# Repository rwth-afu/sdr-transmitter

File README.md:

## Components

### Microcontroller: ST STM32F429VGT6
- ARM Cortex M4 core with DSP and FPU
- 180 MHz cpu clock
- 1 MB flash memory
- 2x 1Msps 12 bit D/A converters (up to 5Msps, see [AN4566](http://www.st.com/resource/en/application_note/dm00129215.pdf))
- USB 2.0 controller
- 10/100 Ethernet MAC
- [Datasheet](http://www.st.com/resource/en/datasheet/stm32f427vg.pdf)

### IQ Modulator: Analog Devices ADRF6755
- Integrated fractional-N PLL & VCO
- Gain control span: 47 dB in 1 dB steps
- Frequency Range: 100 - 2400 MHz
- P1dB (typ @ 1800 MHz): 8 dBm
- Baseband modulation bandwidth: 600 MHz
- [Datasheet](http://www.analog.com/media/en/technical-documentation/data-sheets/ADRF6755.pdf)

### PA Driver: NXP BGA7027
- Frequency Range: 400 - 2700 MHz
- Gain (typ @ 940 MHz): 19 dB
- P1dB (typ @ 940 MHz): 29 dBm
- [Datasheet](https://www.nxp.com/docs/en/data-sheet/BGA7027.pdf)

### Power Amplifier: NXP AFT09MS015N
- Frequency Range: 136 - 941 MHz
- Power Output (typ): 16 W
- Gain (typ): 17 dB
- [Datasheet](https://www.nxp.com/docs/en/data-sheet/AFT09MS015N.pdf)

### Power Detector: Analog Devices AD8364 (*optional*)
- Frequency Range: LF - 2700 MHz
- Dual-channel and channel difference output port
- 60 dB dynamic range
- Maximum input level: 12 dBm
- [Datasheet](http://www.analog.com/media/en/technical-documentation/data-sheets/AD8364.pdf)

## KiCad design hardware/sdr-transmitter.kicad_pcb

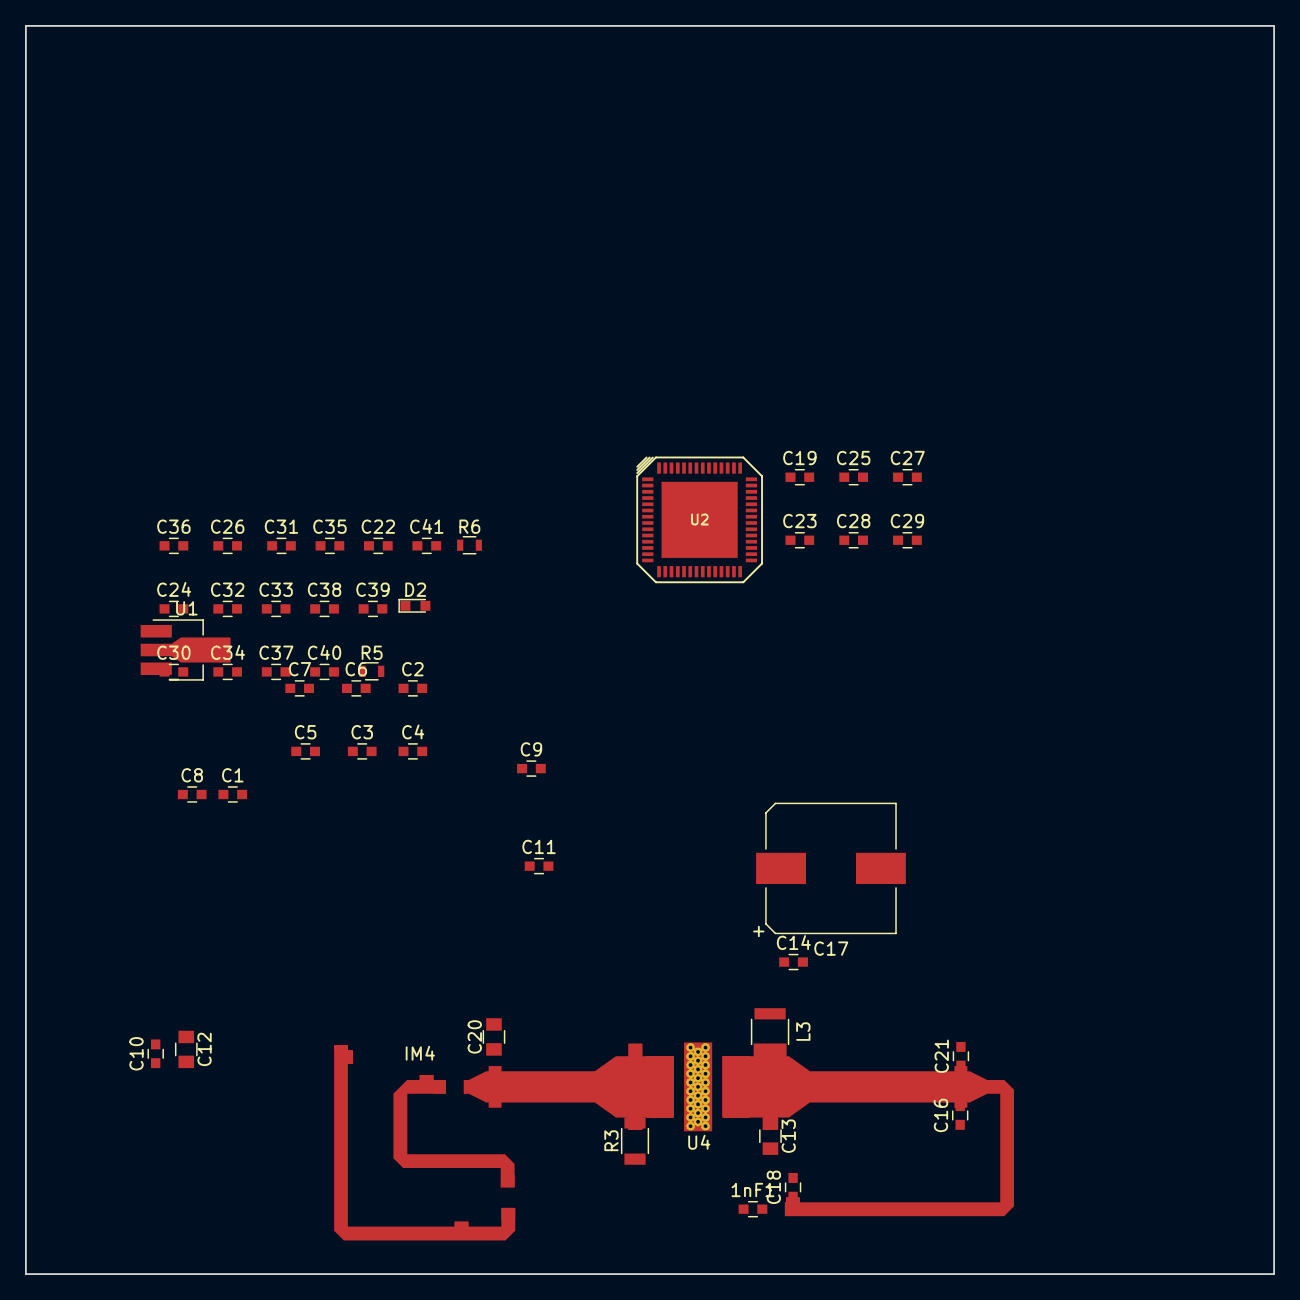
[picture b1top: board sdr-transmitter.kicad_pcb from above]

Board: 2 copper layers, 100.0 x 100.0 mm, 53 parts (0 on the bottom side), 17 nets, no tracks yet.

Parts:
1nF1: C; C_0603
C1, C8: 1nF; C_0603
C2: 10pF; C_0603
C3: 33pF; C_0603
C4, C10, C19, C22, C24, C26, C28, C30, C31, C32, C34, C36, C38, C40: 100n; C_0603
C5: 100nF; C_0603
C6: 100pF; C_0603
C7, C23, C25, C27, C29, C33, C35, C37, C39, C41: 10p; C_0603
C9: 1uF; C_0603
C11: 2.2uF; C_0603
C12: 18pF; C_0805
C13: 10nF; C_0805
C14: 100p; C_0603
C16, C21: 24pF; C_0603
C17: 330uF; CP_Elec_10x10.5
C18: 9.1pF; C_0603
C20: 91p; C_0805
D2: LED; LED_0603
IM1: PA_Input_Match
IM2: PA_Output_Match
IM3: Driver_Input_Match
IM4: Driver_Output_Match
L3: 33nH; L_1210
R3: 100; R_1206
R5: 4k7; R_0603
R6: 100; R_0603
U1: BGA7027; SOT-89-3_Handsoldering
U2: ADRF6755; ANALOG-LFCSP-VQ-56
U4: AFT09MS015N; PLD-1.5W

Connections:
+5V: C4.2, C5.1, C6.1, C7.2, C22.2, C23.2, C24.2, C25.2, C26.2, C27.2, U2.1, U2.11, U2.41, U2.42, U2.55, U2.56
GND: C2.2, C3.2, C4.1, C5.2, C6.2, C7.1, C9.2, C10.2, C11.2, C12.2, C14.2, C16.1, C17.2, C18.2, C19.1, C20.2, C21.2, C22.1, C23.1, C24.1, C25.1, C26.1, C27.1, C28.1, C29.1, C30.1, C31.1, C32.1, C33.1, C34.1, C35.1, C36.1, C37.1, C38.1, C39.1, C40.1, C41.1, D2.1, R5.1, U1.2, U2.6, U2.19, U2.20, U2.21, U2.22, U2.23, U2.24, U2.32, U2.37, U2.39, U2.40, U2.46, U2.47, U2.49, U2.50, U2.51, U2.52, U2.53, U2.54, U2.57, U4.3
unnamed: C12.1, IM1.1
unnamed: C13.2, R3.1
unnamed: C19.2, C29.2, C32.2, C33.2, C34.2, C35.2, C36.2, C37.2, C38.2, C39.2, C40.2, C41.2, U2.12, U2.13, U2.14, U2.15, U2.16, U2.25, U2.26, U2.31, U2.36
unnamed: C21.1, IM2.1
unnamed: C28.2, U2.33
unnamed: C30.2, U2.34
unnamed: C31.2, U2.35
unnamed: D2.2, R6.1
unnamed: R3.2, U4.2
unnamed: L3.2, U4.1
unnamed: IM3.1, U1.3
unnamed: IM4.1, U1.1
unnamed: R5.2, U2.7
unnamed: R6.2, U2.44
VCC: C9.1, C10.1, C14.1, C17.1

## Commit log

2017-12-08 Add PA schematic
2018-05-30 Update PA matching circuits
